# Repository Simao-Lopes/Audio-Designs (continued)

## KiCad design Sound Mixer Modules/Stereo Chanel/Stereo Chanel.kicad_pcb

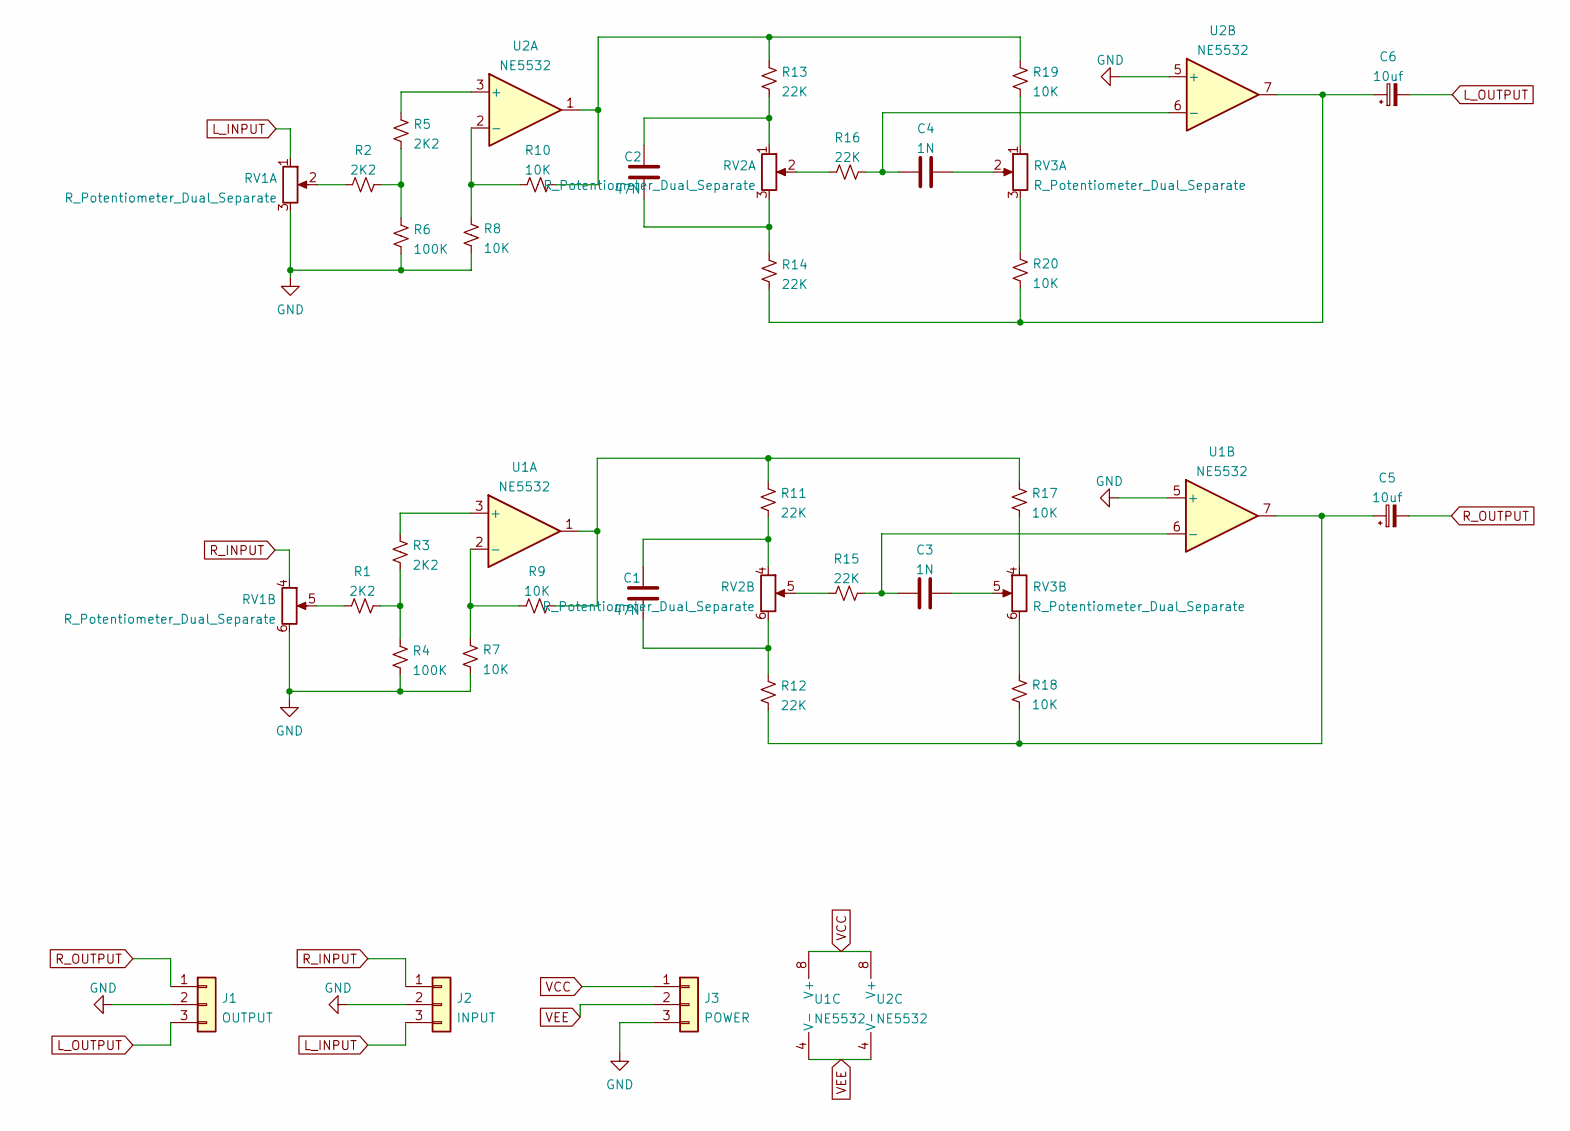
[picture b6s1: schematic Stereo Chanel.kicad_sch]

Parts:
C1, C2: 47N; C_1210_3225Metric
C3, C4: 1N; C_1210_3225Metric
C5, C6: 10uf; CP_Elec_6.3x5.4_Nichicon
J1: OUTPUT; JST_EH_B3B-EH-A_1x03_P2.50mm_Vertical
J2: INPUT; JST_EH_B3B-EH-A_1x03_P2.50mm_Vertical
J3: POWER; JST_EH_B3B-EH-A_1x03_P2.50mm_Vertical
R1, R2, R3, R5: 2K2; R_0805_2012Metric
R4, R6: 100K; R_0805_2012Metric
R7, R8, R9, R10, R17, R18, R19, R20: 10K; R_0805_2012Metric
R11, R12, R13, R14, R15, R16: 22K; R_0805_2012Metric
RV1: R_Potentiometer_Dual_Separate; ALPS RS60112
RV2, RV3: R_Potentiometer_Dual_Separate; Potentiometer_Alpha_RD902F-40-00D_Dual_Vertical
U1, U2: NE5532; DIP-8_W7.62mm_Socket

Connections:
GND: J1.2, J2.2, J3.3, R4.1, R6.1, R7.1, R8.1, RV1.3, RV1.6, U1.5 (+), U2.5 (+); also elsewhere on the board
L_INPUT: J2.3, RV1.1
L_OUTPUT: C6.2, J1.3; also elsewhere on the board
unnamed: C1.1, R11.1, RV2.4
unnamed: C1.2, R12.2, RV2.6
unnamed: C2.1, R13.1, RV2.1
unnamed: C2.2, R14.2, RV2.3
unnamed: C3.1, R15.1, U1.6 (-)
unnamed: C3.2, RV3.5
unnamed: C4.1, R16.1, U2.6 (-)
unnamed: C4.2, RV3.2
unnamed: C5.1, R12.1, R18.1, U1.7
unnamed: C6.1, R14.1, R20.1, U2.7
unnamed: R1.1, RV1.5
unnamed: R1.2, R3.1, R4.2
unnamed: R2.1, RV1.2
unnamed: R2.2, R5.1, R6.2
unnamed: R3.2, U1.3 (+)
unnamed: R5.2, U2.3 (+)
unnamed: R7.2, R9.2, U1.2 (-)
unnamed: R10.1, R13.2, R19.2, U2.1
unnamed: R8.2, R10.2, U2.2 (-)
unnamed: R9.1, R11.2, R17.2, U1.1
unnamed: R15.2, RV2.5
unnamed: R16.2, RV2.2
unnamed: R17.1, RV3.4
unnamed: R18.2, RV3.6
unnamed: R19.1, RV3.1
unnamed: R20.2, RV3.3
R_INPUT: J2.1, RV1.4
R_OUTPUT: C5.2, J1.1; also elsewhere on the board
VCC: J3.1, U1.8 (V+), U2.8 (V+); also elsewhere on the board
VEE: J3.2, U1.4 (V-), U2.4 (V-); also elsewhere on the board

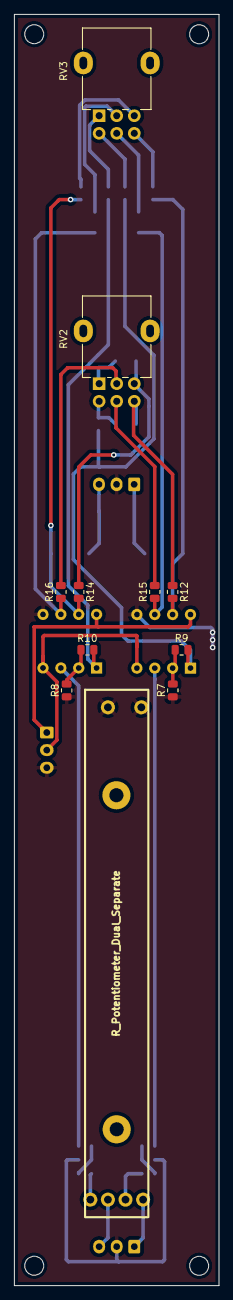
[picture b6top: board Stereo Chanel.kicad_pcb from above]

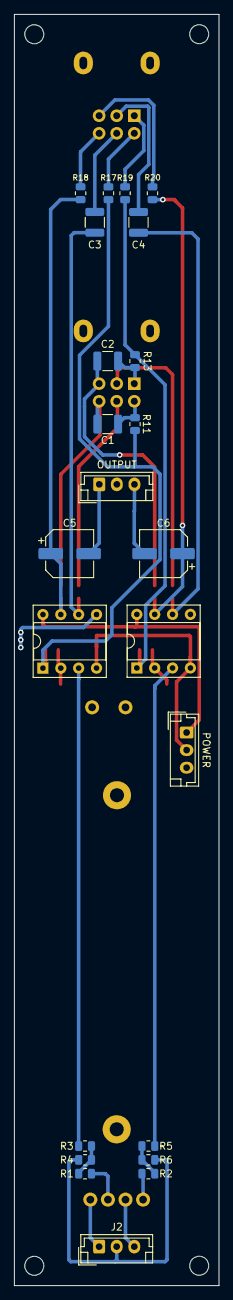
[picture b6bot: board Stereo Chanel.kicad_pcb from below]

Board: 2 copper layers, 29.1 x 180.8 mm, 34 parts (23 on the bottom side), 33 nets.

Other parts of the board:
OUTPUT: OUTPUT; JST_EH_B3B-EH-A_1x03_P2.50mm_Vertical
POWER: POWER; JST_EH_B3B-EH-A_1x03_P2.50mm_Vertical

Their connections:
GND: OUTPUT.2, POWER.3; also elsewhere on the board
L_OUTPUT: OUTPUT.3; also elsewhere on the board
R_OUTPUT: OUTPUT.1; also elsewhere on the board
VCC: POWER.1; also elsewhere on the board
VEE: POWER.2; also elsewhere on the board
